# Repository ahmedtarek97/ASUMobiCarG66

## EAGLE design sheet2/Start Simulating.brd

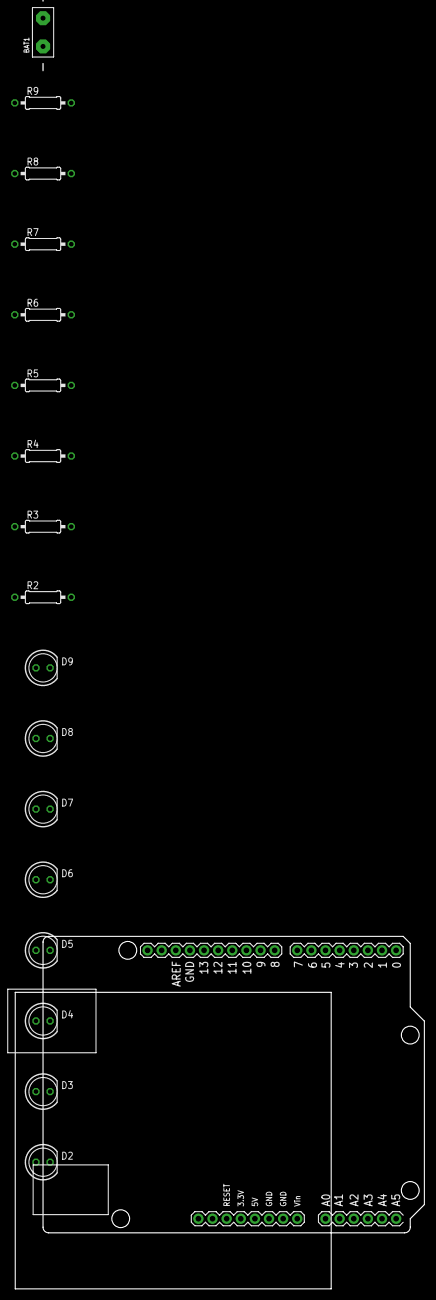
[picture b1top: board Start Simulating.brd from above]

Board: 2 copper layers, 73.6 x 63.4 mm, 18 parts (0 on the bottom side), 19 nets, no tracks yet.

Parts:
BAT1: DC-POWER
D2, D3, D4, D5, D6, D7, D8, D9: LED5MM
R2, R3, R4, R5, R6, R7, R8, R9: 220‎Ω; 0207/10
U3: ARDUINO_UNO

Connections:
unnamed: D9.K, R9.2
unnamed: D8.K, R8.2
unnamed: D7.K, R7.2
unnamed: D6.K, R6.2
unnamed: D2.K, R5.2
unnamed: D3.K, R4.2
unnamed: D4.K, R3.2
unnamed: D5.K, R2.2
unnamed: D5.A, U3.9
unnamed: D4.A, U3.8
unnamed: D3.A, U3.7
unnamed: D2.A, U3.6
unnamed: D6.A, U3.5
unnamed: D7.A, U3.4
unnamed: D8.A, U3.3
unnamed: D9.A, U3.2
unnamed: R2.1, R3.1, R4.1, R5.1, R6.1, R7.1, R8.1, R9.1, U3.GND.
unnamed: BAT1.+, U3.VIN
unnamed: BAT1.-, U3.GND..

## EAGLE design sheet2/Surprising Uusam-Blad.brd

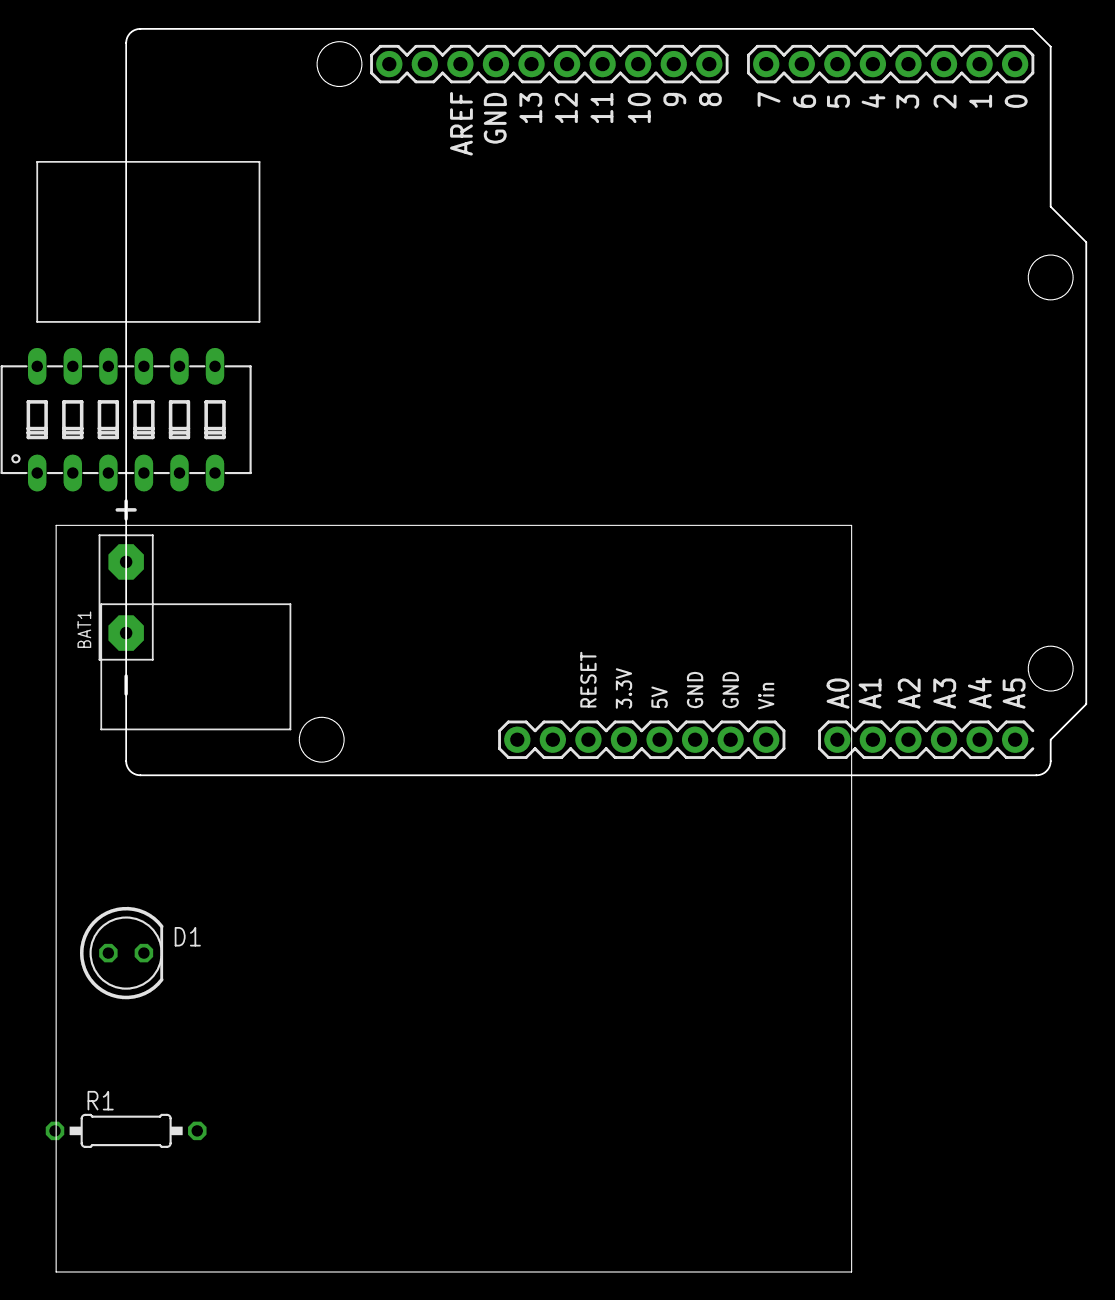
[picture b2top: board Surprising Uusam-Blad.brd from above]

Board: 2 copper layers, 73.6 x 88.8 mm, 5 parts (0 on the bottom side), 11 nets, no tracks yet.

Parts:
BAT1: DC-POWER
D1: LED5MM
R1: 200‎Ω; 0207/10
SW1: DIP06YL
U1: ARDUINO_UNO

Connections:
unnamed: R1.1, U1.13
unnamed: D1.K, R1.2
unnamed: D1.A, U1.GND.
unnamed: BAT1.+, U1.VIN
unnamed: BAT1.-, U1.GND..
unnamed: SW1.1, U1.7
unnamed: SW1.2, U1.6
unnamed: SW1.3, U1.5
unnamed: SW1.4, U1.4
unnamed: SW1.5, U1.3
unnamed: SW1.6, U1.2

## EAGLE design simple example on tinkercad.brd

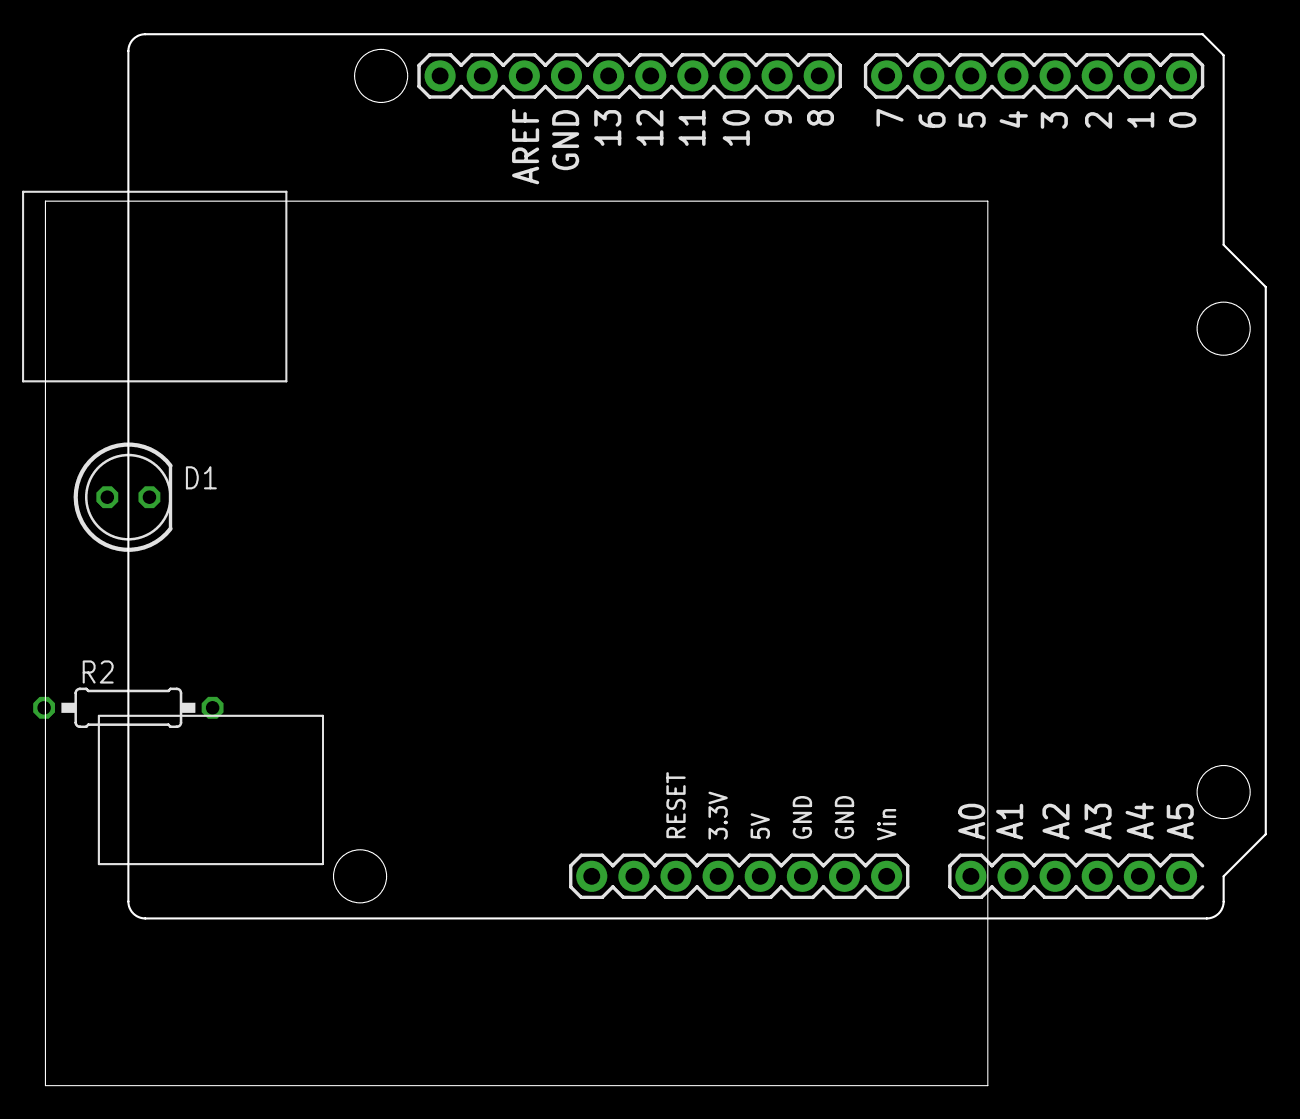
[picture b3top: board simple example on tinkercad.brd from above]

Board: 2 copper layers, 73.6 x 63.4 mm, 3 parts (0 on the bottom side), 3 nets, no tracks yet.

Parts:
D1: LED5MM
R2: 220‎Ω; 0207/10
U1: ARDUINO_UNO

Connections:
unnamed: D1.K, U1.GND..
unnamed: R2.2, U1.13
unnamed: D1.A, R2.1
